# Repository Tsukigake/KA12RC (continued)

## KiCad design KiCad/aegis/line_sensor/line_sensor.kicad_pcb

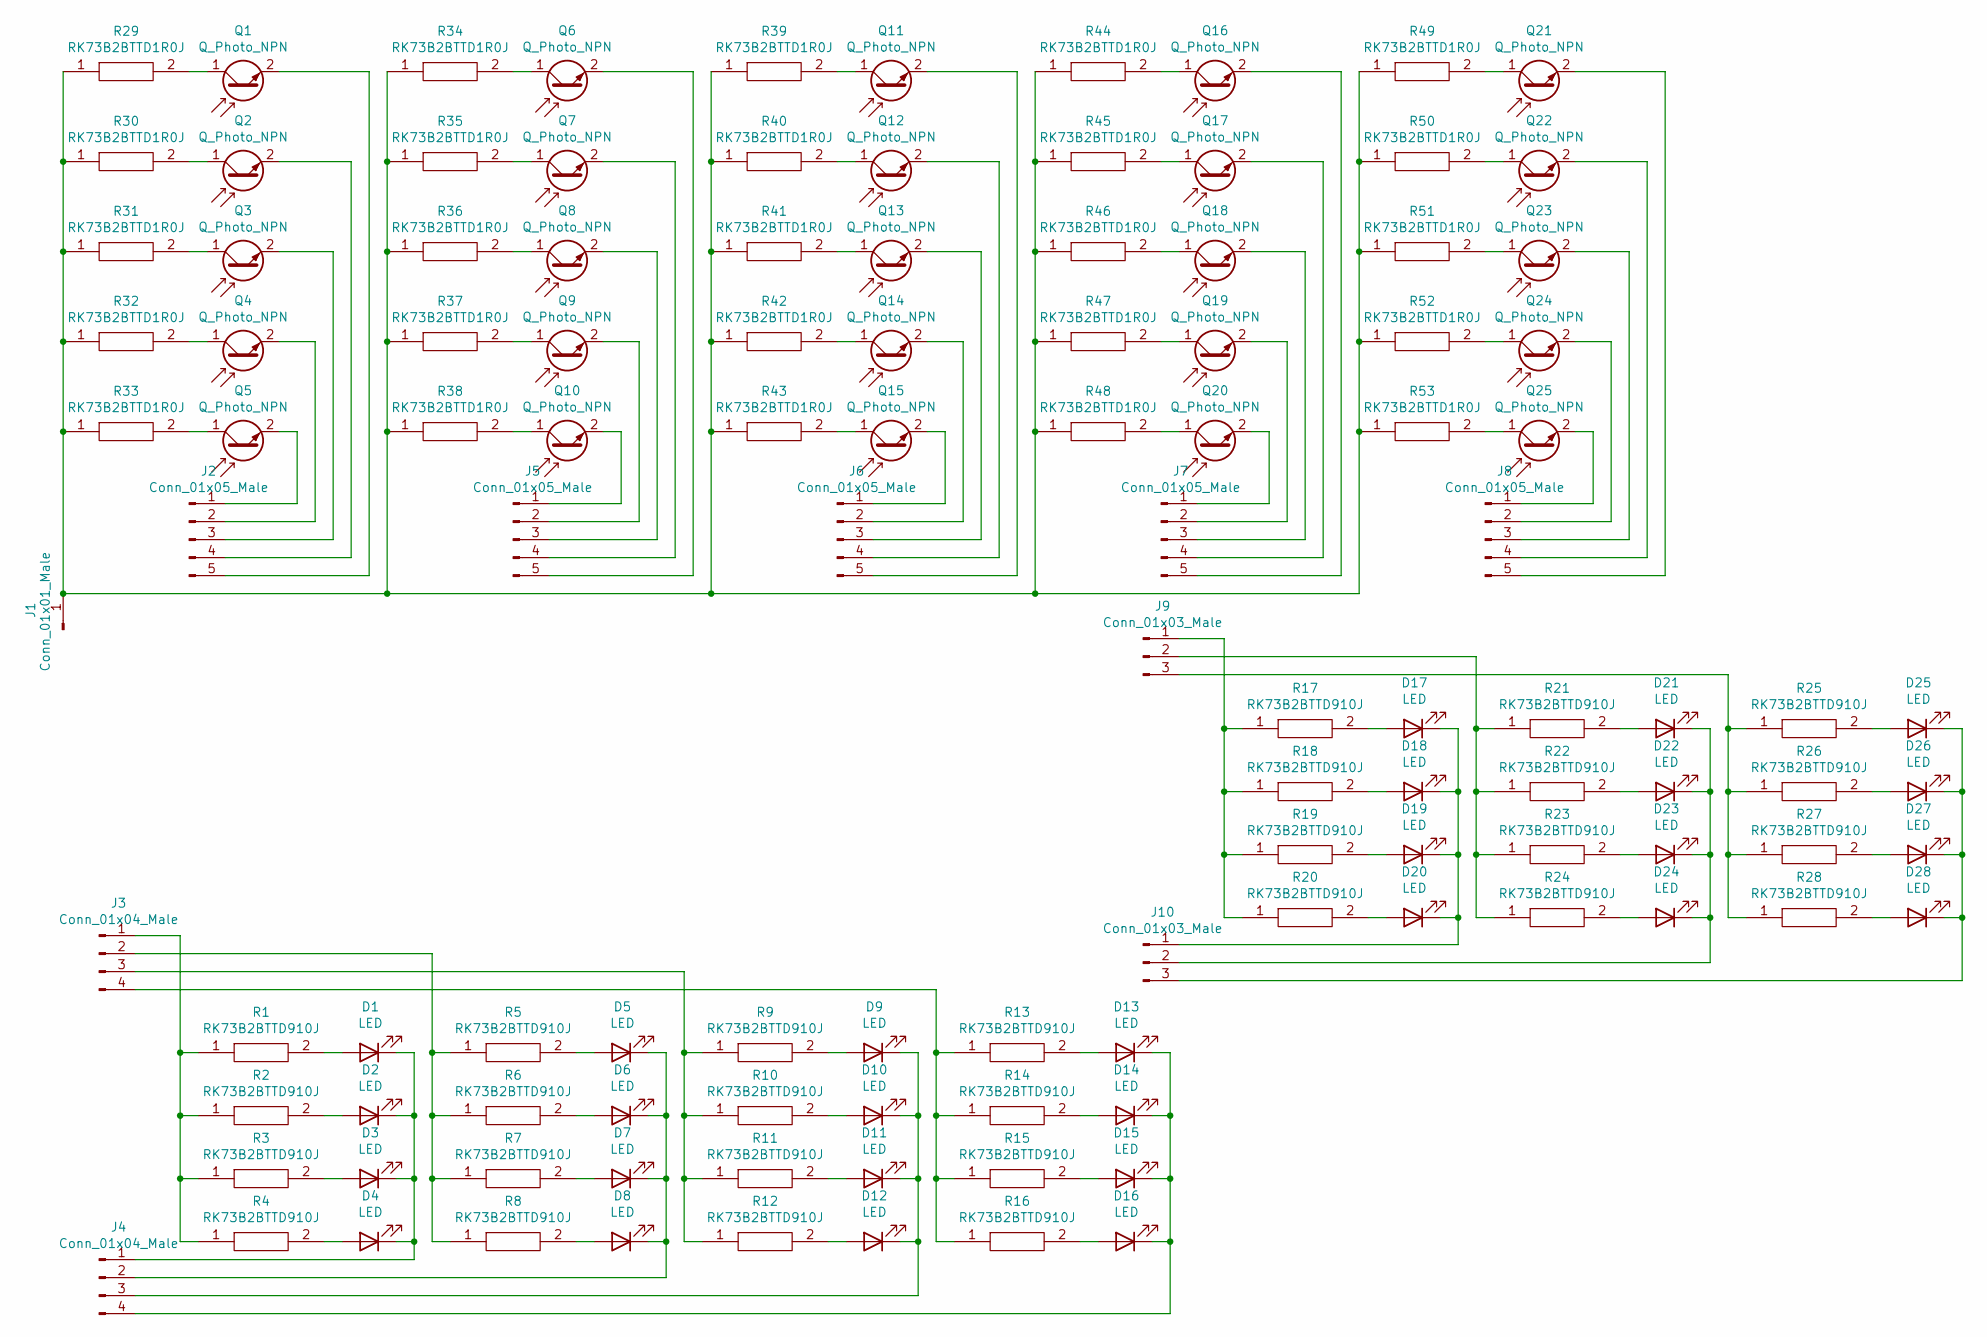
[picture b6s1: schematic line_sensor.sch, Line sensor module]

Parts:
D1, D2, D3, D4, D5, D6, D7, D8, D9, D10, D11, D12, D13, D14, D15, D16, D17, D18, D19, D20, D21, D22, D23, D24, D25, D26, D27, D28: LED; LED_D3.0mm_Clear
J1: Conn_01x01_Male; PinHeader_1x01_P2.54mm_Vertical
J2, J5, J6, J7, J8: Conn_01x05_Male; PinHeader_1x05_P2.54mm_Vertical
J3, J4: Conn_01x04_Male; PinHeader_1x04_P2.54mm_Vertical
J9, J10: Conn_01x03_Male; PinHeader_1x03_P2.54mm_Vertical
Q1, Q2, Q3, Q4, Q5, Q6, Q7, Q8, Q9, Q10, Q11, Q12, Q13, Q14, Q15, Q16, Q17, Q18, Q19, Q20, Q21, Q22, Q23, Q24, Q25: Q_Photo_NPN; NJL7502L
R1, R2, R3, R4, R5, R6, R7, R8, R9, R10, R11, R12, R13, R14, R15, R16, R17, R18, R19, R20, R21, R22, R23, R24, R25, R26, R27, R28: RK73B2BTTD910J; RESC3216X70N; Manufacturer_Part_Number RK73B2BTTD910J
R29, R30, R31, R32, R33, R34, R35, R36, R37, R38, R39, R40, R41, R42, R43, R44, R45, R46, R47, R48, R49, R50, R51, R52, R53: RK73B2BTTD1R0J; RESC3216X80N; Manufacturer_Part_Number RK73B2BTTD1R0J

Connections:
unnamed: D1.1 (K), D2.1 (K), D3.1 (K), D4.1 (K), J4.1
unnamed: D1.2 (A), R1.2
unnamed: D2.2 (A), R2.2
unnamed: D3.2 (A), R3.2
unnamed: D4.2 (A), R4.2
unnamed: D5.1 (K), D6.1 (K), D7.1 (K), D8.1 (K), J4.2
unnamed: D5.2 (A), R5.2
unnamed: D6.2 (A), R6.2
unnamed: D7.2 (A), R7.2
unnamed: D8.2 (A), R8.2
unnamed: D9.2 (A), R9.2
unnamed: D9.1 (K), D10.1 (K), D11.1 (K), D12.1 (K), J4.3
unnamed: D10.2 (A), R10.2
unnamed: D11.2 (A), R11.2
unnamed: D12.2 (A), R12.2
unnamed: D13.1 (K), D14.1 (K), D15.1 (K), D16.1 (K), J4.4
unnamed: D13.2 (A), R13.2
unnamed: D14.2 (A), R14.2
unnamed: D15.2 (A), R15.2
unnamed: D16.2 (A), R16.2
unnamed: D17.1 (K), D18.1 (K), D19.1 (K), D20.1 (K), J10.1
unnamed: D17.2 (A), R17.2
unnamed: D18.2 (A), R18.2
unnamed: D19.2 (A), R19.2
unnamed: D20.2 (A), R20.2
unnamed: D21.1 (K), D22.1 (K), D23.1 (K), D24.1 (K), J10.2
unnamed: D21.2 (A), R21.2
unnamed: D22.2 (A), R22.2
unnamed: D23.2 (A), R23.2
unnamed: D24.2 (A), R24.2
unnamed: D25.1 (K), D26.1 (K), D27.1 (K), D28.1 (K), J10.3
unnamed: D25.2 (A), R25.2
unnamed: D26.2 (A), R26.2
unnamed: D27.2 (A), R27.2
unnamed: D28.2 (A), R28.2
unnamed: J1.1, R29.1, R30.1, R31.1, R32.1, R33.1, R34.1, R35.1, R36.1, R37.1, R38.1, R39.1, R40.1, R41.1, R42.1, R43.1, R44.1, R45.1, R46.1, R47.1, R48.1, R49.1, R50.1, R51.1, R52.1, R53.1
unnamed: J2.1, Q5.2 (E)
unnamed: J2.2, Q4.2 (E)
unnamed: J2.3, Q3.2 (E)
unnamed: J2.4, Q2.2 (E)
unnamed: J2.5, Q1.2 (E)
unnamed: J3.1, R1.1, R2.1, R3.1, R4.1
unnamed: J3.2, R5.1, R6.1, R7.1, R8.1
unnamed: J3.3, R9.1, R10.1, R11.1, R12.1
unnamed: J3.4, R13.1, R14.1, R15.1, R16.1
unnamed: J5.1, Q10.2 (E)
unnamed: J5.2, Q9.2 (E)
unnamed: J5.3, Q8.2 (E)
unnamed: J5.4, Q7.2 (E)
unnamed: J5.5, Q6.2 (E)
unnamed: J6.1, Q15.2 (E)
unnamed: J6.2, Q14.2 (E)
unnamed: J6.3, Q13.2 (E)
unnamed: J6.4, Q12.2 (E)
unnamed: J6.5, Q11.2 (E)
unnamed: J7.1, Q20.2 (E)
unnamed: J7.2, Q19.2 (E)
unnamed: J7.3, Q18.2 (E)
unnamed: J7.4, Q17.2 (E)
unnamed: J7.5, Q16.2 (E)
unnamed: J8.1, Q25.2 (E)
unnamed: J8.2, Q24.2 (E)
unnamed: J8.3, Q23.2 (E)
unnamed: J8.4, Q22.2 (E)
unnamed: J8.5, Q21.2 (E)
unnamed: J9.1, R17.1, R18.1, R19.1, R20.1
unnamed: J9.2, R21.1, R22.1, R23.1, R24.1
unnamed: J9.3, R25.1, R26.1, R27.1, R28.1
unnamed: Q1.1 (C), R29.2
unnamed: Q2.1 (C), R30.2
unnamed: Q3.1 (C), R31.2
unnamed: Q4.1 (C), R32.2
unnamed: Q5.1 (C), R33.2
unnamed: Q6.1 (C), R34.2
unnamed: Q7.1 (C), R35.2
unnamed: Q8.1 (C), R36.2
unnamed: Q9.1 (C), R37.2
unnamed: Q10.1 (C), R38.2
unnamed: Q11.1 (C), R39.2
unnamed: Q12.1 (C), R40.2
unnamed: Q13.1 (C), R41.2
unnamed: Q14.1 (C), R42.2
unnamed: Q15.1 (C), R43.2
unnamed: Q16.1 (C), R44.2
unnamed: Q17.1 (C), R45.2
unnamed: Q18.1 (C), R46.2
unnamed: Q19.1 (C), R47.2
unnamed: Q20.1 (C), R48.2
unnamed: Q21.1 (C), R49.2
unnamed: Q22.1 (C), R50.2
unnamed: Q23.1 (C), R51.2
unnamed: Q24.1 (C), R52.2
unnamed: Q25.1 (C), R53.2

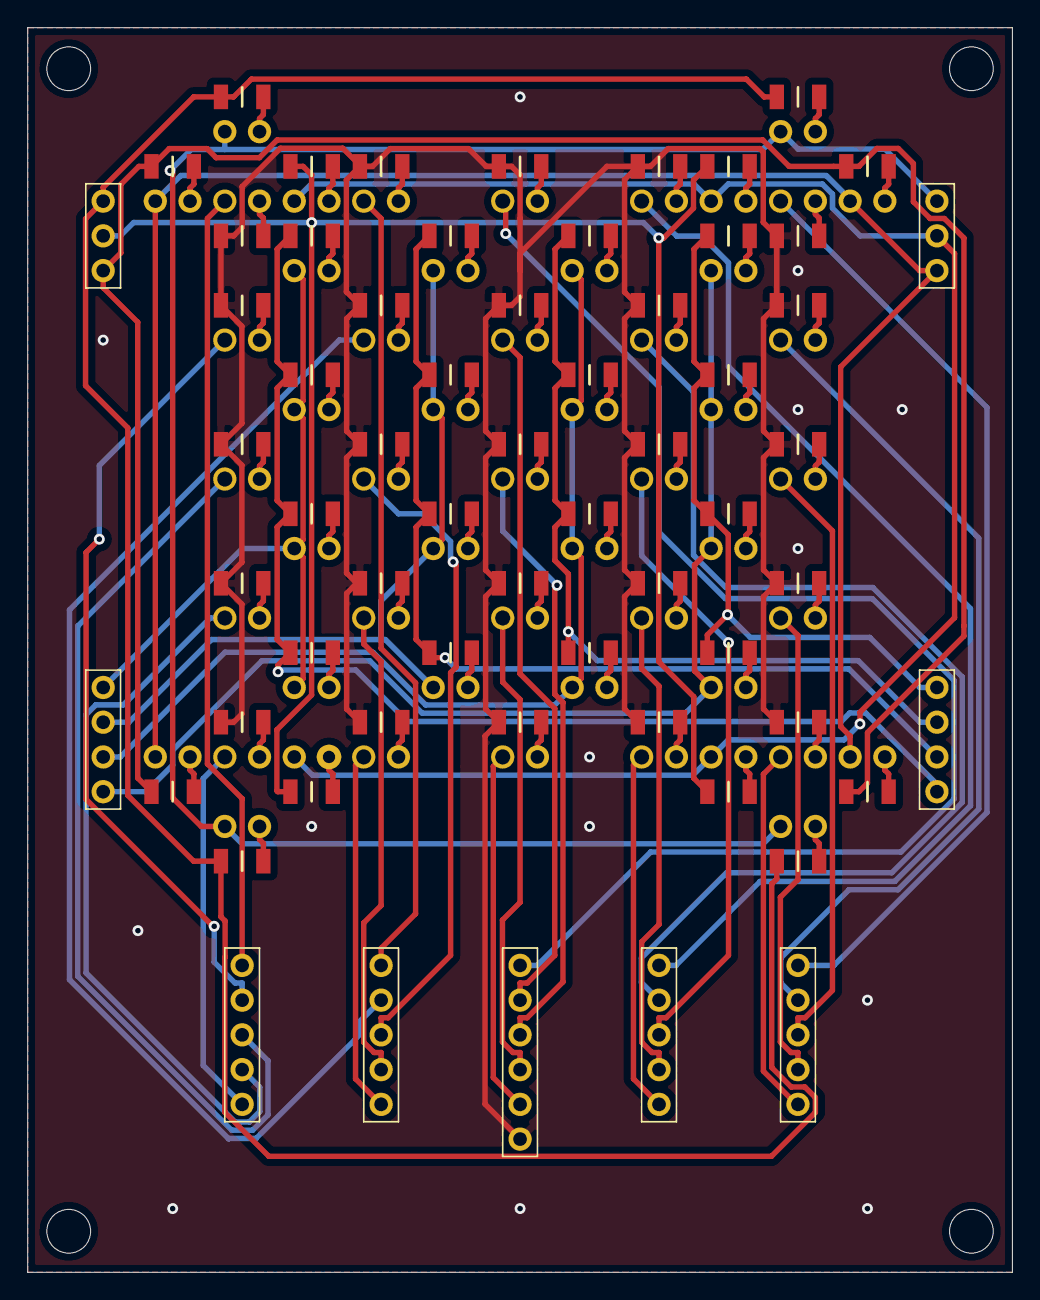
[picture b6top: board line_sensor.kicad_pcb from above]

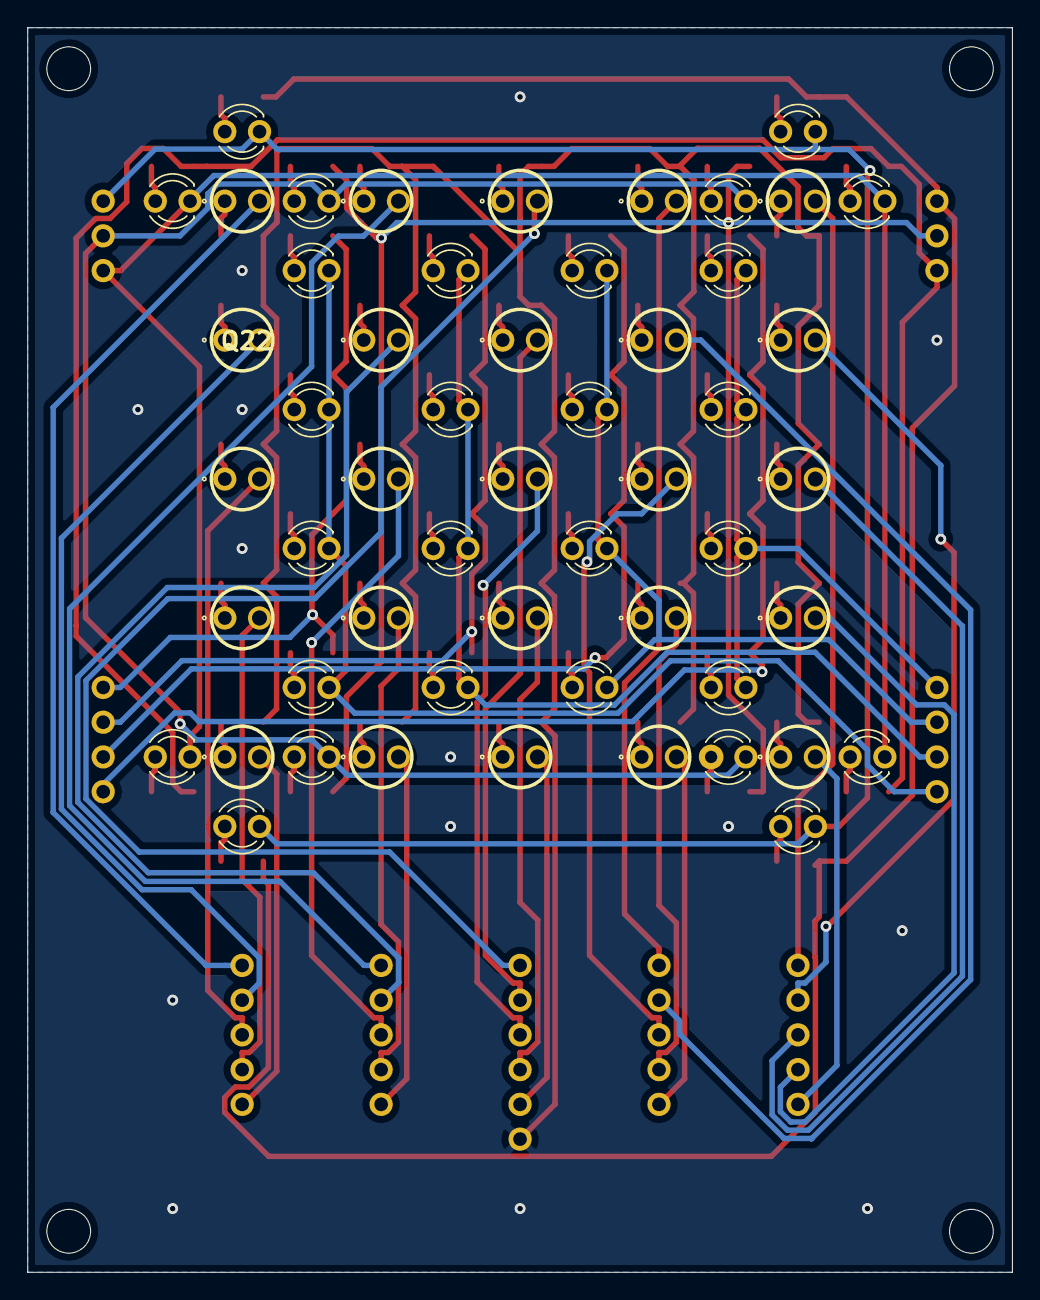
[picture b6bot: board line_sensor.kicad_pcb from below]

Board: 2 copper layers, 72.0 x 91.0 mm, 116 parts (53 on the bottom side), 93 nets.

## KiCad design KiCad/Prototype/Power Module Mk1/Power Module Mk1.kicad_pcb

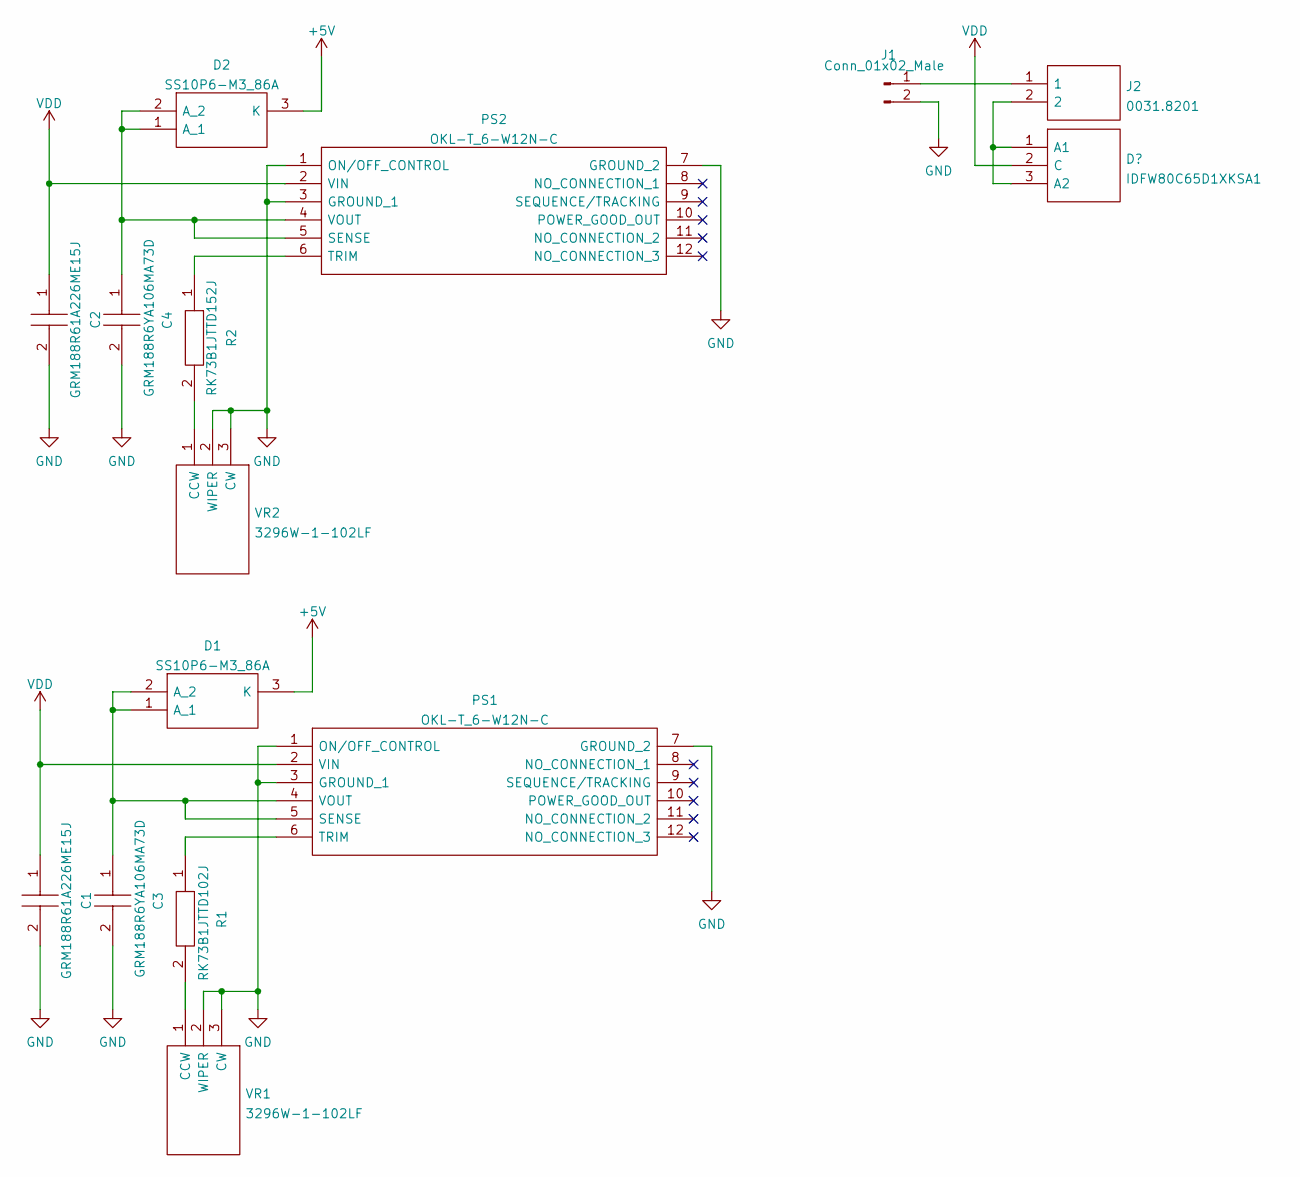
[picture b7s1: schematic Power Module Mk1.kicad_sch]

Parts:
C1, C2: GRM188R61A226ME15J; CAPC1608X90N; Manufacturer_Part_Number GRM188R61A226ME15J
C3, C4: GRM188R6YA106MA73D; CAPC1608X90N; Manufacturer_Part_Number GRM188R6YA106MA73D
D1, D2: SS10P6-M3_86A; SS10P6M386A; Manufacturer_Part_Number SS10P6-M3/86A
J1: Conn_01x02_Male; JST_XH_B2B-XH-A_1x02_P2.50mm_Vertical
J2: 0031.8201; Manufacturer_Part_Number 0031.8201
PS1, PS2: OKL-T_6-W12N-C; OKLT6W12NC; Manufacturer_Part_Number OKL-T/6-W12N-C
R1: RK73B1JTTD102J; RESC1608X55N; Manufacturer_Part_Number RK73B1JTTD102J
R2: RK73B1JTTD152J; RESC1608X55N; Manufacturer_Part_Number RK73B1JTTD152J
VR1, VR2: 3296W-1-102LF; 3296W1102LF; Manufacturer_Part_Number 3296W-1-102LF

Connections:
+5V: D1.3 (K), D2.3 (K)
GND: C1.2, C2.2, C3.2, C4.2, J1.2, PS1.1 (ON/OFF_CONTROL), PS1.3 (GROUND_1), PS1.7 (GROUND_2), PS2.1 (ON/OFF_CONTROL), PS2.3 (GROUND_1), PS2.7 (GROUND_2), VR1.2 (WIPER), VR1.3 (CW), VR2.2 (WIPER), VR2.3 (CW)
unnamed: C3.1, D1.1 (A_1), D1.2 (A_2), PS1.4 (VOUT), PS1.5 (SENSE)
unnamed: C4.1, D2.1 (A_1), D2.2 (A_2), PS2.4 (VOUT), PS2.5 (SENSE)
unnamed: J1.1, J2.1
unnamed: PS1.6 (TRIM), R1.1
unnamed: PS2.6 (TRIM), R2.1
unnamed: R1.2, VR1.1 (CCW)
unnamed: R2.2, VR2.1 (CCW)
VDD: C1.1, C2.1, J2.2, PS1.2 (VIN), PS2.2 (VIN)

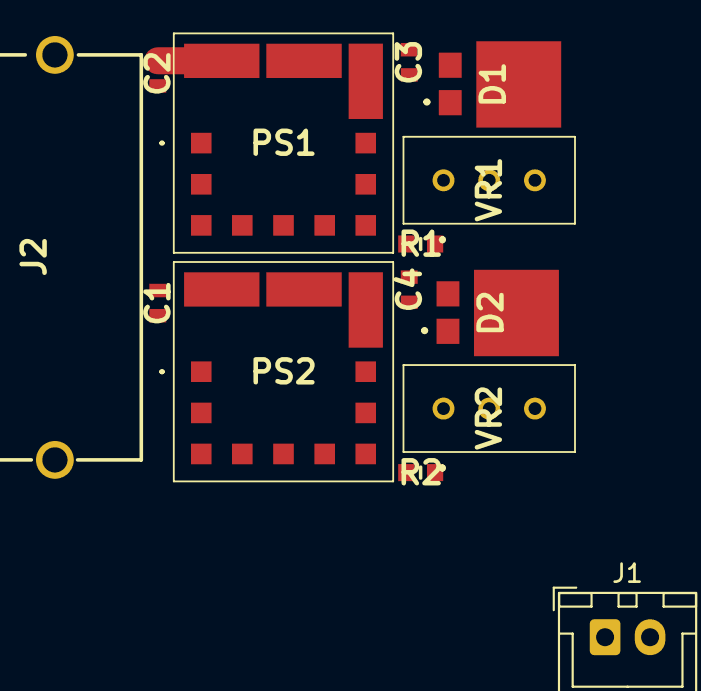
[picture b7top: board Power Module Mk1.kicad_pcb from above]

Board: 2 copper layers, 14 parts (0 on the bottom side), 10 nets.

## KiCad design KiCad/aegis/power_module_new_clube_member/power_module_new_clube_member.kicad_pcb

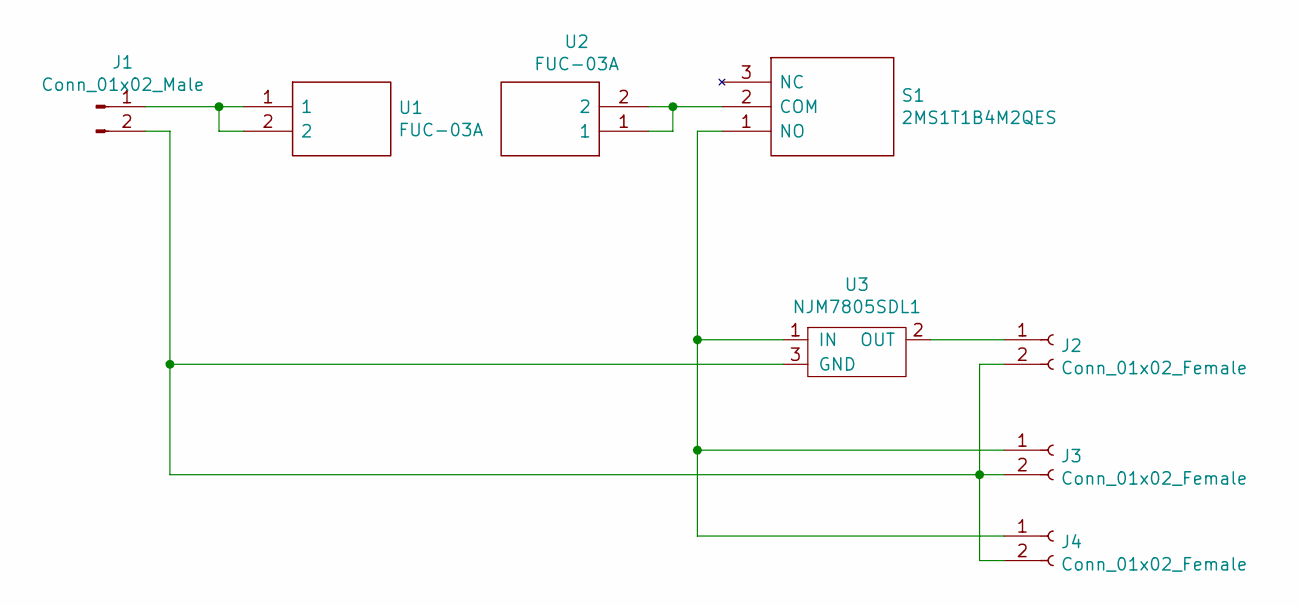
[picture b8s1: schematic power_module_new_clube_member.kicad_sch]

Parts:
J1: Conn_01x02_Male; JST_XH_B2B-XH-A_1x02_P2.50mm_Vertical
J2, J3: Conn_01x02_Female; JST_XH_B2B-XH-A_1x02_P2.50mm_Vertical
J4: Conn_01x02_Female; PinHeader_1x02_P2.54mm_Vertical
S1: 2MS1T1B4M2QES; Manufacturer_Part_Number 2MS1T1B4M2QES
U1, U2: FUC-03A; FUC03A; Manufacturer_Part_Number FUC-03A
U3: NJM7805SDL1

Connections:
unnamed: J1.1, U1.1, U1.2
unnamed: J1.2, J2.2, J3.2, J4.2, U3.3 (GND)
unnamed: J2.1, U3.2 (OUT)
unnamed: J3.1, J4.1, S1.1 (NO), U3.1 (IN)
unnamed: S1.2 (COM), U2.1, U2.2

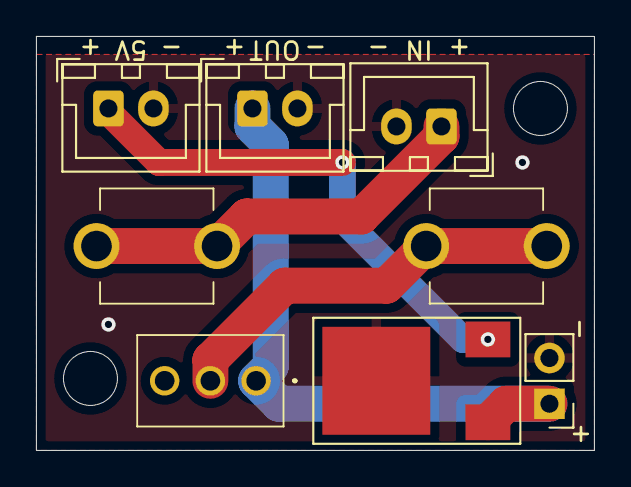
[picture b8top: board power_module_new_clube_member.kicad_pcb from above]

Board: 2 copper layers, 31.0 x 23.0 mm, 8 parts (0 on the bottom side), 5 nets.
